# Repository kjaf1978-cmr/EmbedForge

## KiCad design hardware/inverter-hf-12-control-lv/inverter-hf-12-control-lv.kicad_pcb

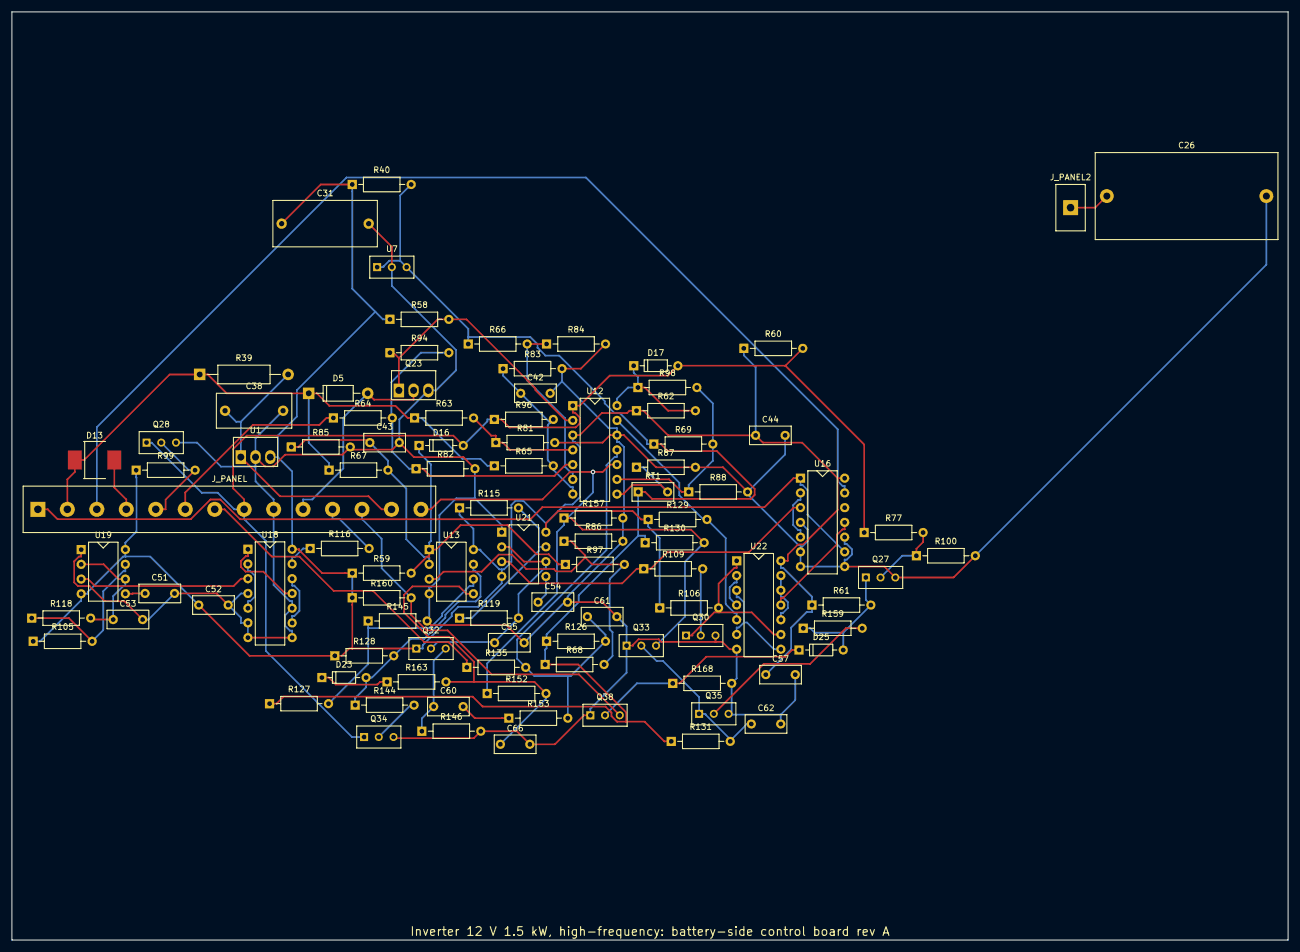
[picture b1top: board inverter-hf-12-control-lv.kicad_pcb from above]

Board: 2 copper layers, 220.0 x 160.0 mm, 96 parts (0 on the bottom side), 61 nets.

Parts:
C26: 33u; C_Film_P27.5
C31: 22u; C_Film_P15
C38: 10u; C_Film_P10
C42, C43: 470n; C_Disc_5.08
C44, C52, C53, C57, C60: 100n; C_Disc_5.08
C51, C54: 10n; C_Disc_5.08
C55: 1n; C_Disc_5.08
C61: 470p; C_Disc_5.08
C62, C66: 220n; C_Disc_5.08
D5: 1N4007; D_DO-41
D13: SS34; D_SMC
D16, D17, D23, D25: 1N4148; D_DO-35
J_PANEL: to the panel; TerminalBlock_1x14
J_PANEL2: to the panel; TerminalBlock_1x1
Q23: IRF540N; TO-220_Vertical
Q27, Q28, Q30, Q32, Q34, Q35: BC547B; TO-92_Wide
Q33: BC557B; TO-92_Wide
Q38: 2N7000; TO-92_Wide
R39: 1; R_Axial_0309
R40, R116: 2.2k; R_Axial_0207
R58, R59, R60, R61, R62, R81, R82, R83, R84, R85, R86, R87, R105, R109, R127, R128, R130, R160, R163: 10k; R_Axial_0207
R63: 49.9k; R_Axial_0207
R64: 45.3k; R_Axial_0207
R65: 39.2k; R_Axial_0207
R66: 1.54k; R_Axial_0207
R67: 51.1k; R_Axial_0207
R68: 715; R_Axial_0207
R69: 3.92k; R_Axial_0207
R77, R100, R144: 47k; R_Axial_0207
R88: 40.2k; R_Axial_0207
R94, R152: 1M; R_Axial_0207
R96: 332k; R_Axial_0207
R97, R131, R159, R168: 100k; R_Axial_0207
R98: 2.2M; R_Axial_0207
R99: 22k; R_Axial_0207
R106, R129, R146: 4.7k; R_Axial_0207
R115: 24.3k; R_Axial_0207
R118: 30.9k; R_Axial_0207
R119: 5.76k; R_Axial_0207
R126: 5.23k; R_Axial_0207
R135: 1k; R_Axial_0207
R145: 30.1k; R_Axial_0207
R153: 3.74k; R_Axial_0207
R157: 33k; R_Axial_0207
RT1: 10k; RT_Disc_5.08
U1: LM2940-9.0; TO-220_Vertical
U7: TL431B; TO-92_Wide
U12: LM339; DIP-14
U13: LM393; DIP-8
U16, U18, U22: V9; DIP-14
U19, U21: NE555; DIP-8

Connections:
A: J_PANEL.1, U16.1, U16.9
AN: U16.2, U16.5
AXA: D5.1, D13.1, J_PANEL.2, R39.1, R63.1, R65.1, R67.1
B: J_PANEL.3, U16.13
BBK: Q30.2, R109.2
BF: D13.2, J_PANEL.4
BKA: J_PANEL.5, Q28.2, R99.2
BLK: Q30.1, R106.2, U22.1, U22.9
BOL: Q34.2, R144.2
BQE: Q27.2, R77.2, R100.1
BSSL: Q35.2, R159.2
BUS: J_PANEL.6, R64.1
C200: U18.3, U19.3
CKB: U16.11, U22.11
CKN: U22.10, U22.12, U22.13
CSF: C61.1, R126.2, R135.2, R153.2, U12.11
CSR: J_PANEL.7, R135.1
D40: R115.2, R119.1, U21.7
D50: R105.2, R118.1, U19.7
ENL: D16.2, D17.2, J_PANEL.8, Q28.1, Q34.1, R60.2, R77.1, R96.1, U12.1
ENNL: D25.2, Q27.1, R61.2, R159.1
GND: C26.2, C31.2, C38.2, C42.2, C43.2, C44.2, C51.2, C52.2, C53.2, C54.2, C55.2, C57.2, C61.2, C62.2, C66.2, J_PANEL.9, Q23.3, Q27.3, Q28.3, Q30.3, Q33.1, Q34.3, Q35.3, Q38.1, R81.2, R82.2, R83.2, R84.2, R85.2, R86.2, R87.2, R88.2, R100.2, R145.2, R146.2, R157.2, R168.2, U1.2, U7.2, U12.12, U13.4, U16.4, U16.6, U16.7, U16.8, U16.10, U18.4, U18.6, U18.7, U18.8, U18.10, U19.1, U21.1, U22.7
HVN: D16.1, R59.2, R97.1, U13.1
K40: C54.1, U21.5
K50: C51.1, U19.5
KC: D5.2, J_PANEL.10, Q23.2
KEN: Q23.1, R58.2, R94.1, U12.2
L50A: J_PANEL.11, R116.2
NHS: R87.1, RT1.2, U12.8
O40: R109.1, U16.3, U21.3
OC: R129.2, U12.13, U22.5
OLF: D23.1, R163.1
OLL: D23.2, R128.2, R144.1, U13.7
Q50: R116.1, U18.13
Q50N: U18.9, U18.12
Q100: U18.1, U18.11
Q100N: U18.2, U18.5
QC: U22.3, U22.6, U22.8
QCN: U22.2, U22.4
SDL: J_PANEL.12, Q38.3, R160.2
SLP: C60.2, R153.1
STOPL: D25.1, Q38.2, R168.1
T40: C55.1, Q32.2, R119.2, U21.2, U21.6
T40E: C60.1, Q32.3, R146.1
T50: C53.1, R118.2, U19.2, U19.6
T90: R69.2, R88.1, R98.2, U12.9
THN: D17.1, R62.2, R98.1, U12.14
V9: C31.1, C44.1, C52.1, C57.1, Q32.1, R40.1, R58.1, R59.1, R60.1, R61.1, R62.1, R99.1, R105.1, R106.1, R115.1, R128.1, R129.1, R160.1, U1.3, U12.3, U13.8, U16.14, U18.14, U19.4, U19.8, U21.4, U21.8, U22.14
V12: C38.1, J_PANEL.13, R39.2, U1.1
VBF: R63.2, R81.1, U12.4
VBH: C43.1, R67.2, R85.1, U13.2
VBS: C42.1, R65.2, R83.1, R96.2, U12.7
VBU: R64.2, R82.1, R94.2, U12.5
VC: J_PANEL.14, Q33.3, R130.2, R152.1, R157.1, U12.10
VCF: C66.1, R152.2, R163.2, U13.5
VHI: R68.2, R86.1, R97.2, U13.3
VLO: R66.2, R84.1, U12.6
VOT: R127.2, R145.1, U13.6
VREFL: R40.2, R66.1, R68.1, R69.1, R126.1, R127.1, R130.1, R131.1, RT1.1, U7.1, U7.3
VSSL: C62.1, Q33.2, Q35.1, R131.2
XB: C26.1, J_PANEL2.1

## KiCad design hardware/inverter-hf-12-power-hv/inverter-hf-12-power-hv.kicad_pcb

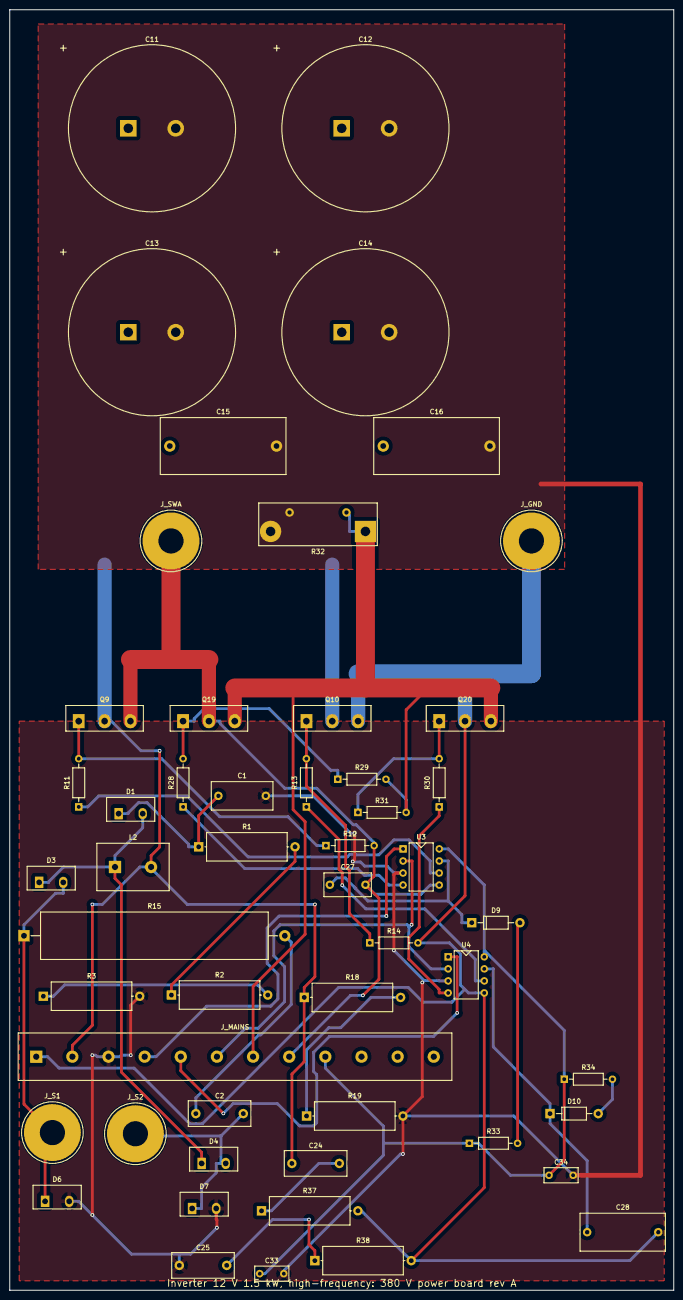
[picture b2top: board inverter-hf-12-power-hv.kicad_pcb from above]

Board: 2 copper layers, 140.0 x 270.0 mm, 52 parts (0 on the bottom side), 31 nets.

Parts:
C1: 100n; C_Film_P10
C2: 220p; C_Disc_P10
C11, C12, C13, C14: 470u; CP_SnapIn_D35
C15, C16: 2.2u; C_Film_P22.5
C24, C25: 2.2n; C_Disc_P10
C27: 2.2u; C_Film_P7.5
C28: 22u; C_Film_P15
C33, C34: 1u; C_Disc_5.08
D1: C4D02120A; TO-220-2_Vertical
D3, D4, D6, D7: C4D20120A; TO-220-2_Vertical
D9, D10: UF4007; D_DO-41
J_GND: GND; Lug_M5
J_MAINS: mains to the panel; TerminalBlock_1x12_P7.62
J_S1: S1; Lug_M5
J_S2: S2; Lug_M5
J_SWA: SWA; Lug_M5
L2: 470u; TerminalBlock_1x2_P7.62
Q9, Q10, Q19, Q20: IKW50N60T; TO-247_Vertical
R1, R2, R3: 150k; R_Axial_P20
R11, R13, R28, R30, R34: 10; R_Axial_0207
R12, R14, R29, R31: 10k; R_Axial_0207
R15: 470; R_Cement_10W
R18, R19: 47k; R_Axial_P20
R32: 4.99m; R_Shunt_4T
R33: 2.2; R_Axial_0207
R37, R38: 220; R_Axial_P20
U3, U4: IR2184-type 600 V; DIP-8

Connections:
BLM: R18.2, R19.1
CL: C1.1, D1.1, R1.1
CL1: R1.2, R2.1
CL2: R2.2, R3.1
GIHA: Q9.1, R11.2, R12.1
GIHB: Q10.1, R13.2, R14.1
GILA: Q19.1, R28.2, R29.1
GILB: Q20.1, R30.2, R31.1
GND: C28.2, J_GND.1, J_MAINS.1, Q10.3, Q20.2, R14.2, R37.2, R38.2, U4.5
HBUS: C11.1, C12.1, C13.1, C14.1, C15.1, C16.1, C24.1, J_MAINS.2, L2.2, Q9.2, Q10.2, R18.1
HOIA: R11.1, U3.6
HOIB: R13.1, U4.6
HVG: C1.2, C11.2, C12.2, C13.2, C14.2, C15.2, C16.2, C25.1, C33.2, C34.2, D6.2, D7.2, J_MAINS.3, R3.2, R19.2, R32.2, R32.4, U3.3, U4.3
INA: J_MAINS.4, U3.1
INB: J_MAINS.5, U4.1
LOIA: R28.1, U3.4
LOIB: R30.1, U4.4
RP: D1.2, D3.1, D4.1, L2.1
S1: D3.2, D6.1, J_S1.1, R15.1
S2: C2.2, D4.2, D7.1, J_S2.1
SD: J_MAINS.6, U3.2, U4.2
SNB: C2.1, R15.2
SRC: J_MAINS.7, Q19.3, Q20.3, R29.2, R31.2, R32.1, R32.3
SWA: C27.2, J_MAINS.8, J_SWA.1, Q9.3, Q19.2, R12.2, U3.5
V15H: C33.1, C34.1, J_MAINS.9, R33.1, R34.1, U3.8, U4.8
VBIA: C27.1, D9.1, U3.7
VBIB: C28.1, D10.1, U4.7
VBRA: D9.2, R33.2
VBRB: D10.2, R34.2
YD1: C24.2, R37.1
YD2: C25.2, R38.1

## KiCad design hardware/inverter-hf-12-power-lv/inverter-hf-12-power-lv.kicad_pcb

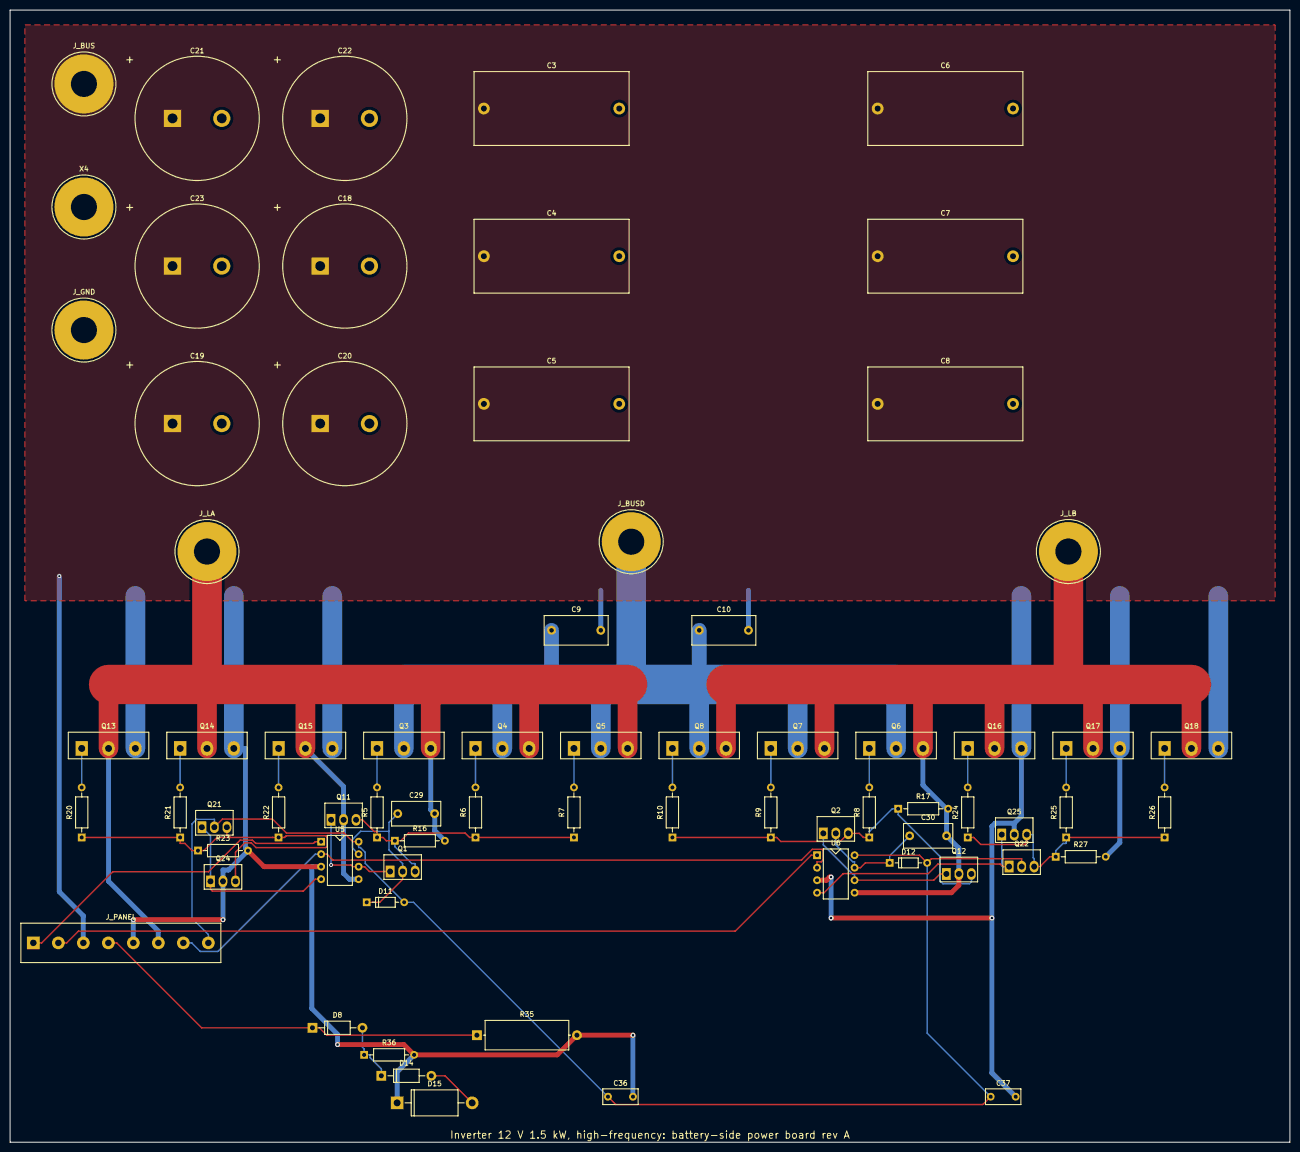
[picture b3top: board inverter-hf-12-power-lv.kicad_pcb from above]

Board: 2 copper layers, 260.0 x 230.0 mm, 70 parts (0 on the bottom side), 34 nets.

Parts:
C3, C4, C5, C6, C7, C8: 47u; C_Film_P27.5
C9, C10: 2.2u; C_Film_P10
C18, C19, C20, C21, C22, C23: 4700u; CP_SnapIn_D25
C29, C30: 2.2u; C_Film_P7.5
C36, C37: 1u; C_Disc_5.08
D8, D14: UF4007; D_DO-41
D11, D12: 1N4148; D_DO-35
D15: 1N5359B; D_DO-201AD
J_BUS: BUS; Lug_M5
J_BUSD: BUSD; Lug_M5
J_GND: GND; Lug_M5
J_LA: LA; Lug_M5
J_LB: LB; Lug_M5
J_PANEL: to the panel; TerminalBlock_1x8
Q1, Q2, Q21, Q22: D44H11; TO-220_Vertical
Q3, Q4, Q5, Q6, Q7, Q8, Q13, Q14, Q15, Q16, Q17, Q18: IRFP4468; TO-247_Vertical
Q11, Q12, Q24, Q25: D45H11; TO-220_Vertical
R5, R6, R7, R8, R9, R10, R20, R21, R22, R24, R25, R26: 4.7; R_Axial_0207
R16, R17, R23, R27: 10k; R_Axial_0207
R35: 0.68; R_Axial_P20
R36: 1k; R_Axial_0207
U5, U6: IR2184-type 600 V; DIP-8
X4: BAT-; Lug_M5

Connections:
A: J_PANEL.1, U5.1
B: J_PANEL.2, U6.1
BUS: C3.1, C4.1, C5.1, C6.1, C7.1, C8.1, C18.1, C19.1, C20.1, C21.1, C22.1, C23.1, J_BUS.1, J_PANEL.3
BUSD: C9.1, C10.1, J_BUSD.1, Q3.2, Q4.2, Q5.2, Q6.2, Q7.2, Q8.2
CSR: D8.1, J_PANEL.4, R35.1
CTA: D8.2, D14.1, R36.1
CZC: D14.2, D15.2
EHA: Q1.3, Q11.3, R5.1, R6.1, R7.1, R16.1
EHB: Q2.3, Q12.3, R8.1, R9.1, R10.1, R17.1
ELA: Q21.3, Q24.3, R20.1, R21.1, R22.1, R23.1
ELB: Q22.3, Q25.3, R24.1, R25.1, R26.1, R27.1
GHA1: Q3.1, R5.2
GHA2: Q4.1, R6.2
GHA3: Q5.1, R7.2
GHB1: Q6.1, R8.2
GHB2: Q7.1, R9.2
GHB3: Q8.1, R10.2
GLA1: Q13.1, R20.2
GLA2: Q14.1, R21.2
GLA3: Q15.1, R22.2
GLB1: Q16.1, R24.2
GLB2: Q17.1, R25.2
GLB3: Q18.1, R26.2
GND: C3.2, C4.2, C5.2, C6.2, C7.2, C8.2, C9.2, C10.2, C18.2, C19.2, C20.2, C21.2, C22.2, C23.2, C36.2, C37.2, D15.1, J_GND.1, J_PANEL.5, Q13.3, Q14.3, Q15.3, Q16.3, Q17.3, Q18.3, Q24.2, Q25.2, R23.2, R27.2, R35.2, R36.2, U5.3, U6.3, X4.1
HOA: Q1.1, Q11.1, U5.6
HOB: Q2.1, Q12.1, U6.6
LA: C29.2, J_LA.1, J_PANEL.6, Q3.3, Q4.3, Q5.3, Q11.2, Q13.2, Q14.2, Q15.2, R16.2, U5.5
LB: C30.2, J_LB.1, Q6.3, Q7.3, Q8.3, Q12.2, Q16.2, Q17.2, Q18.2, R17.2, U6.5
LOA: Q21.1, Q24.1, U5.4
LOB: Q22.1, Q25.1, U6.4
SDL: J_PANEL.7, U5.2, U6.2
V12: C36.1, C37.1, D11.2, D12.2, J_PANEL.8, Q21.2, Q22.2, U5.8, U6.8
VBA: C29.1, D11.1, Q1.2, U5.7
VBB: C30.1, D12.1, Q2.2, U6.7

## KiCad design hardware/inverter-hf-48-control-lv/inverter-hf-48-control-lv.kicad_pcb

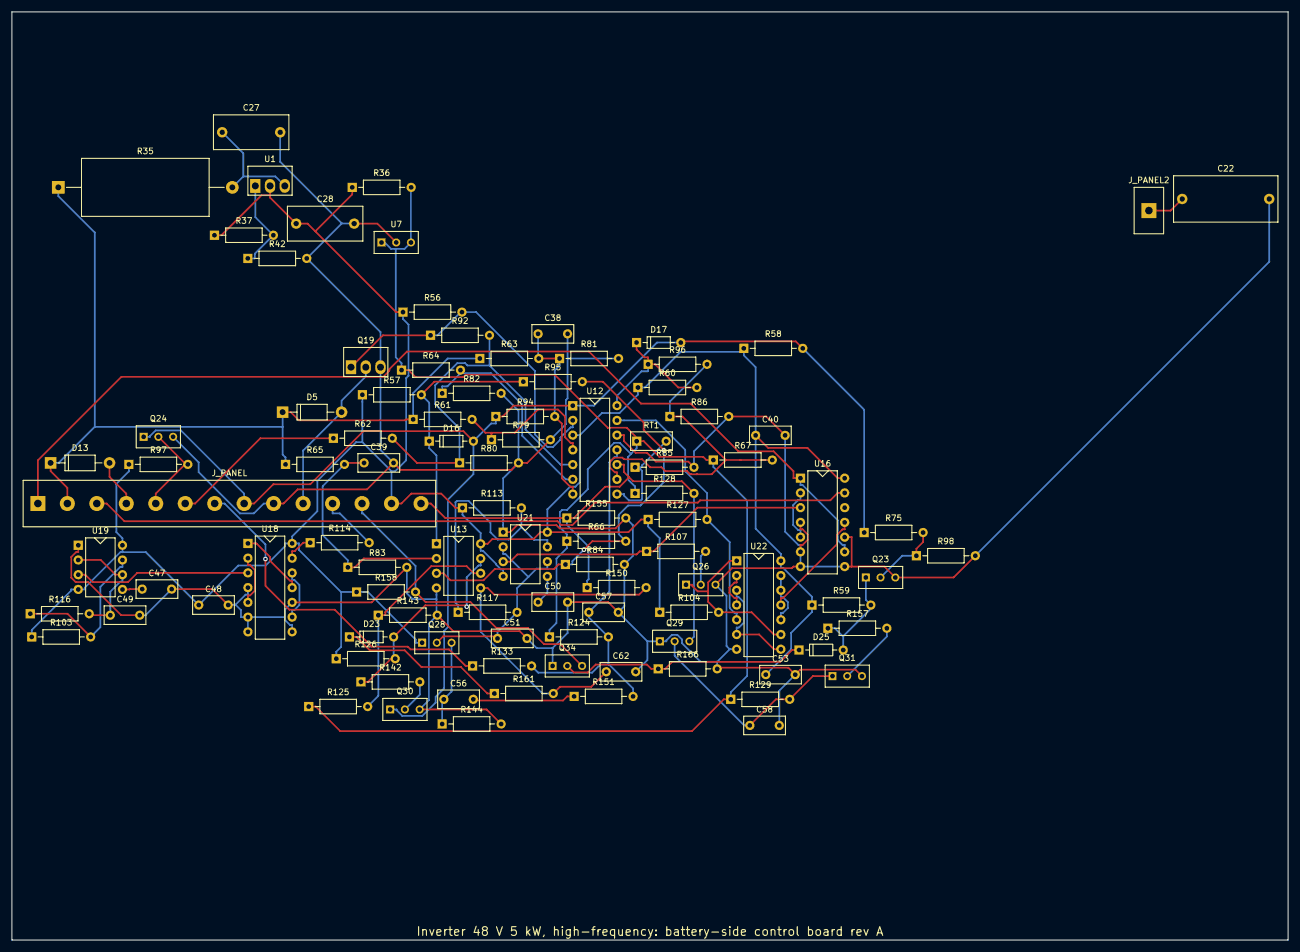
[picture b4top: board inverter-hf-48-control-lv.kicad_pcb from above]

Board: 2 copper layers, 220.0 x 160.0 mm, 98 parts (0 on the bottom side), 62 nets.

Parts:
C22: 2.2u; C_Film_P15
C27: 2.2u; C_Film_P10
C28: 10u; C_Film_P10
C38, C39: 470n; C_Disc_5.08
C40, C48, C49, C53, C56: 100n; C_Disc_5.08
C47, C50: 10n; C_Disc_5.08
C51: 1n; C_Disc_5.08
C57: 470p; C_Disc_5.08
C58, C62: 220n; C_Disc_5.08
D5, D13: 1N4007; D_DO-41
D16, D17, D23, D25: 1N4148; D_DO-35
J_PANEL: to the panel; TerminalBlock_1x14
J_PANEL2: to the panel; TerminalBlock_1x1
Q19: IRF540N; TO-220_Vertical
Q23, Q24, Q26, Q28, Q30, Q31: BC547B; TO-92_Wide
Q29: BC557B; TO-92_Wide
Q34: 2N7000; TO-92_Wide
R35: 220; R_Cement_5W
R36, R114: 2.2k; R_Axial_0207
R37: 240; R_Axial_0207
R42: 2.05k; R_Axial_0207
R56, R57, R58, R59, R60, R79, R80, R81, R82, R83, R84, R85, R103, R107, R125, R126, R128, R158, R161: 10k; R_Axial_0207
R61, R63: 200k; R_Axial_0207
R62: 182k; R_Axial_0207
R64: 1.54k; R_Axial_0207
R65: 243k; R_Axial_0207
R66: 715; R_Axial_0207
R67: 3.92k; R_Axial_0207
R75, R98, R142: 47k; R_Axial_0207
R86: 40.2k; R_Axial_0207
R92, R150: 1M; R_Axial_0207
R94: 475k; R_Axial_0207
R95, R129, R157, R166: 100k; R_Axial_0207
R96: 2.2M; R_Axial_0207
R97: 22k; R_Axial_0207
R104, R127, R144: 4.7k; R_Axial_0207
R113: 24.3k; R_Axial_0207
R116: 30.9k; R_Axial_0207
R117: 5.76k; R_Axial_0207
R124: 5.23k; R_Axial_0207
R133: 1k; R_Axial_0207
R143: 30.1k; R_Axial_0207
R151: 4.99k; R_Axial_0207
R155: 33k; R_Axial_0207
RT1: 10k; RT_Disc_5.08
U1: LM317HV; TO-220_Vertical
U7: TL431B; TO-92_Wide
U12: LM339; DIP-14
U13: LM393; DIP-8
U16, U18, U22: V12; DIP-14
U19, U21: NE555; DIP-8

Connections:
A: J_PANEL.1, U16.1, U16.9
ADJ: R37.2, R42.1, U1.1
AN: U16.2, U16.5
AXA: D5.1, D13.1, J_PANEL.2, R35.1, R61.1, R63.1, R65.1
B: J_PANEL.3, U16.13
BBK: Q26.2, R107.2
BF: D13.2, J_PANEL.4
BKA: J_PANEL.5, Q24.2, R97.2
BLK: Q26.1, R104.2, U22.1, U22.9
BOL: Q30.2, R142.2
BQE: Q23.2, R75.2, R98.1
BSSL: Q31.2, R157.2
BUS: J_PANEL.6, R62.1
C200: U18.3, U19.3
CKB: U16.11, U22.11
CKN: U22.10, U22.12, U22.13
CSF: C57.1, R124.2, R133.2, R151.2, U12.11
CSR: J_PANEL.7, R133.1
D40: R113.2, R117.1, U21.7
D50: R103.2, R116.1, U19.7
ENL: D16.2, D17.2, J_PANEL.8, Q24.1, Q30.1, R58.2, R75.1, R94.1, U12.1
ENNL: D25.2, Q23.1, R59.2, R157.1
GND: C22.2, C27.2, C28.2, C38.2, C39.2, C40.2, C47.2, C48.2, C49.2, C50.2, C51.2, C53.2, C57.2, C58.2, C62.2, J_PANEL.9, Q19.3, Q23.3, Q24.3, Q26.3, Q29.1, Q30.3, Q31.3, Q34.1, R42.2, R79.2, R80.2, R81.2, R82.2, R83.2, R84.2, R85.2, R86.2, R98.2, R143.2, R144.2, R155.2, R166.2, U7.2, U12.12, U13.4, U16.4, U16.6, U16.7, U16.8, U16.10, U18.4, U18.6, U18.7, U18.8, U18.10, U19.1, U21.1, U22.7
HVN: D16.1, R57.2, R95.1, U13.1
K40: C50.1, U21.5
K50: C47.1, U19.5
KC: D5.2, J_PANEL.10, Q19.2
KEN: Q19.1, R56.2, R92.1, U12.2
L50A: J_PANEL.11, R114.2
NHS: R85.1, RT1.2, U12.8
O40: R107.1, U16.3, U21.3
OC: R127.2, U12.13, U22.5
OLF: D23.1, R161.1
OLL: D23.2, R126.2, R142.1, U13.7
Q50: R114.1, U18.13
Q50N: U18.9, U18.12
Q100: U18.1, U18.11
Q100N: U18.2, U18.5
QC: U22.3, U22.6, U22.8
QCN: U22.2, U22.4
SDL: J_PANEL.12, Q34.3, R158.2
SLP: C56.2, R151.1
STOPL: D25.1, Q34.2, R166.1
T40: C51.1, Q28.2, R117.2, U21.2, U21.6
T40E: C56.1, Q28.3, R144.1
T50: C49.1, R116.2, U19.2, U19.6
T90: R67.2, R86.1, R96.2, U12.9
THN: D17.1, R60.2, R96.1, U12.14
V12: C28.1, C40.1, C48.1, C53.1, J_PANEL.13, Q28.1, R36.1, R37.1, R56.1, R57.1, R58.1, R59.1, R60.1, R97.1, R103.1, R104.1, R113.1, R126.1, R127.1, R158.1, U1.2, U12.3, U13.8, U16.14, U18.14, U19.4, U19.8, U21.4, U21.8, U22.14
VBF: R61.2, R79.1, U12.4
VBH: C39.1, R65.2, R83.1, U13.2
VBS: C38.1, R63.2, R81.1, R94.2, U12.7
VBU: R62.2, R80.1, R92.2, U12.5
VC: J_PANEL.14, Q29.3, R128.2, R150.1, R155.1, U12.10
VCF: C62.1, R150.2, R161.2, U13.5
VHI: R66.2, R84.1, R95.2, U13.3
VLO: R64.2, R82.1, U12.6
VOT: R125.2, R143.1, U13.6
VRAW: C27.1, R35.2, U1.3
VREFL: R36.2, R64.1, R66.1, R67.1, R124.1, R125.1, R128.1, R129.1, RT1.1, U7.1, U7.3
VSSL: C58.1, Q29.2, Q31.1, R129.2
XB: C22.1, J_PANEL2.1

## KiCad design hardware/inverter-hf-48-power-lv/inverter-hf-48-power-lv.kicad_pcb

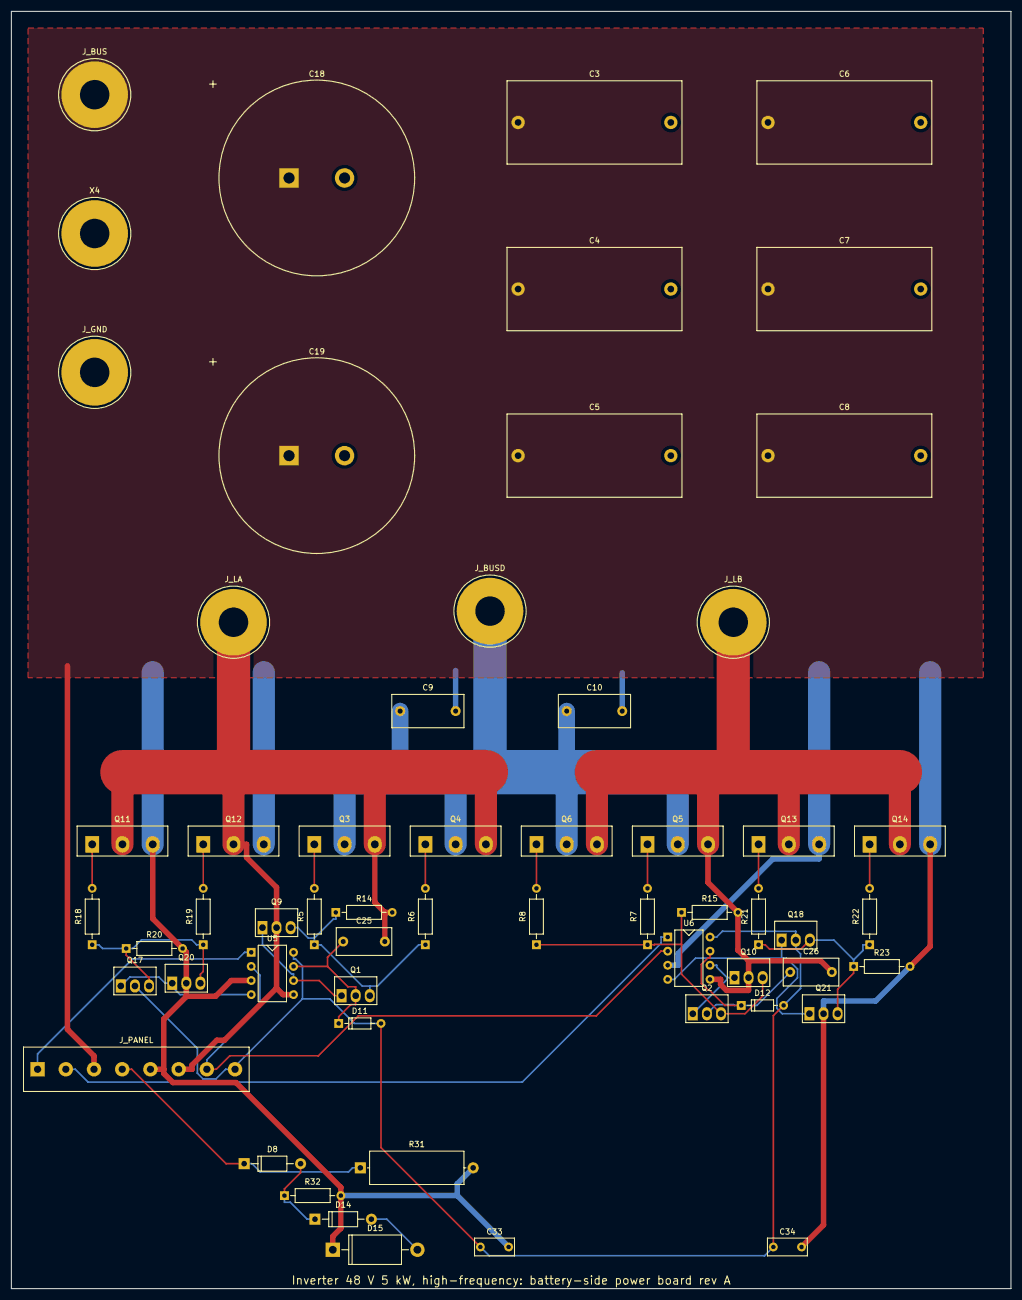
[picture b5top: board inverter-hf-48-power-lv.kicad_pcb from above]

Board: 2 copper layers, 180.0 x 230.0 mm, 58 parts (0 on the bottom side), 30 nets.

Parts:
C3, C4, C5, C6, C7, C8: 47u; C_Film_P27.5
C9, C10: 2.2u; C_Film_P10
C18, C19: 2200u; CP_SnapIn_D35
C25, C26: 2.2u; C_Film_P7.5
C33, C34: 1u; C_Disc_5.08
D8, D14: UF4007; D_DO-41
D11, D12: 1N4148; D_DO-35
D15: 1N5359B; D_DO-201AD
J_BUS: BUS; Lug_M5
J_BUSD: BUSD; Lug_M5
J_GND: GND; Lug_M5
J_LA: LA; Lug_M5
J_LB: LB; Lug_M5
J_PANEL: to the panel; TerminalBlock_1x8
Q1, Q2, Q17, Q18: D44H11; TO-220_Vertical
Q3, Q4, Q5, Q6, Q11, Q12, Q13, Q14: IRFP4468; TO-247_Vertical
Q9, Q10, Q20, Q21: D45H11; TO-220_Vertical
R5, R6, R7, R8, R18, R19, R21, R22: 4.7; R_Axial_0207
R14, R15, R20, R23: 10k; R_Axial_0207
R31: 1.2; R_Axial_P20
R32: 1k; R_Axial_0207
U5, U6: IR2184-type 600 V; DIP-8
X4: BAT-; Lug_M5

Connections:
A: J_PANEL.1, U5.1
B: J_PANEL.2, U6.1
BUS: C3.1, C4.1, C5.1, C6.1, C7.1, C8.1, C18.1, C19.1, J_BUS.1, J_PANEL.3
BUSD: C9.1, C10.1, J_BUSD.1, Q3.2, Q4.2, Q5.2, Q6.2
CSR: D8.1, J_PANEL.4, R31.1
CTA: D8.2, D14.1, R32.1
CZC: D14.2, D15.2
EHA: Q1.3, Q9.3, R5.1, R6.1, R14.1
EHB: Q2.3, Q10.3, R7.1, R8.1, R15.1
ELA: Q17.3, Q20.3, R18.1, R19.1, R20.1
ELB: Q18.3, Q21.3, R21.1, R22.1, R23.1
GHA1: Q3.1, R5.2
GHA2: Q4.1, R6.2
GHB1: Q5.1, R7.2
GHB2: Q6.1, R8.2
GLA1: Q11.1, R18.2
GLA2: Q12.1, R19.2
GLB1: Q13.1, R21.2
GLB2: Q14.1, R22.2
GND: C3.2, C4.2, C5.2, C6.2, C7.2, C8.2, C9.2, C10.2, C18.2, C19.2, C33.2, C34.2, D15.1, J_GND.1, J_PANEL.5, Q11.3, Q12.3, Q13.3, Q14.3, Q20.2, Q21.2, R20.2, R23.2, R31.2, R32.2, U5.3, U6.3, X4.1
HOA: Q1.1, Q9.1, U5.6
HOB: Q2.1, Q10.1, U6.6
LA: C25.2, J_LA.1, J_PANEL.6, Q3.3, Q4.3, Q9.2, Q11.2, Q12.2, R14.2, U5.5
LB: C26.2, J_LB.1, Q5.3, Q6.3, Q10.2, Q13.2, Q14.2, R15.2, U6.5
LOA: Q17.1, Q20.1, U5.4
LOB: Q18.1, Q21.1, U6.4
SDL: J_PANEL.7, U5.2, U6.2
V12: C33.1, C34.1, D11.2, D12.2, J_PANEL.8, Q17.2, Q18.2, U5.8, U6.8
VBA: C25.1, D11.1, Q1.2, U5.7
VBB: C26.1, D12.1, Q2.2, U6.7

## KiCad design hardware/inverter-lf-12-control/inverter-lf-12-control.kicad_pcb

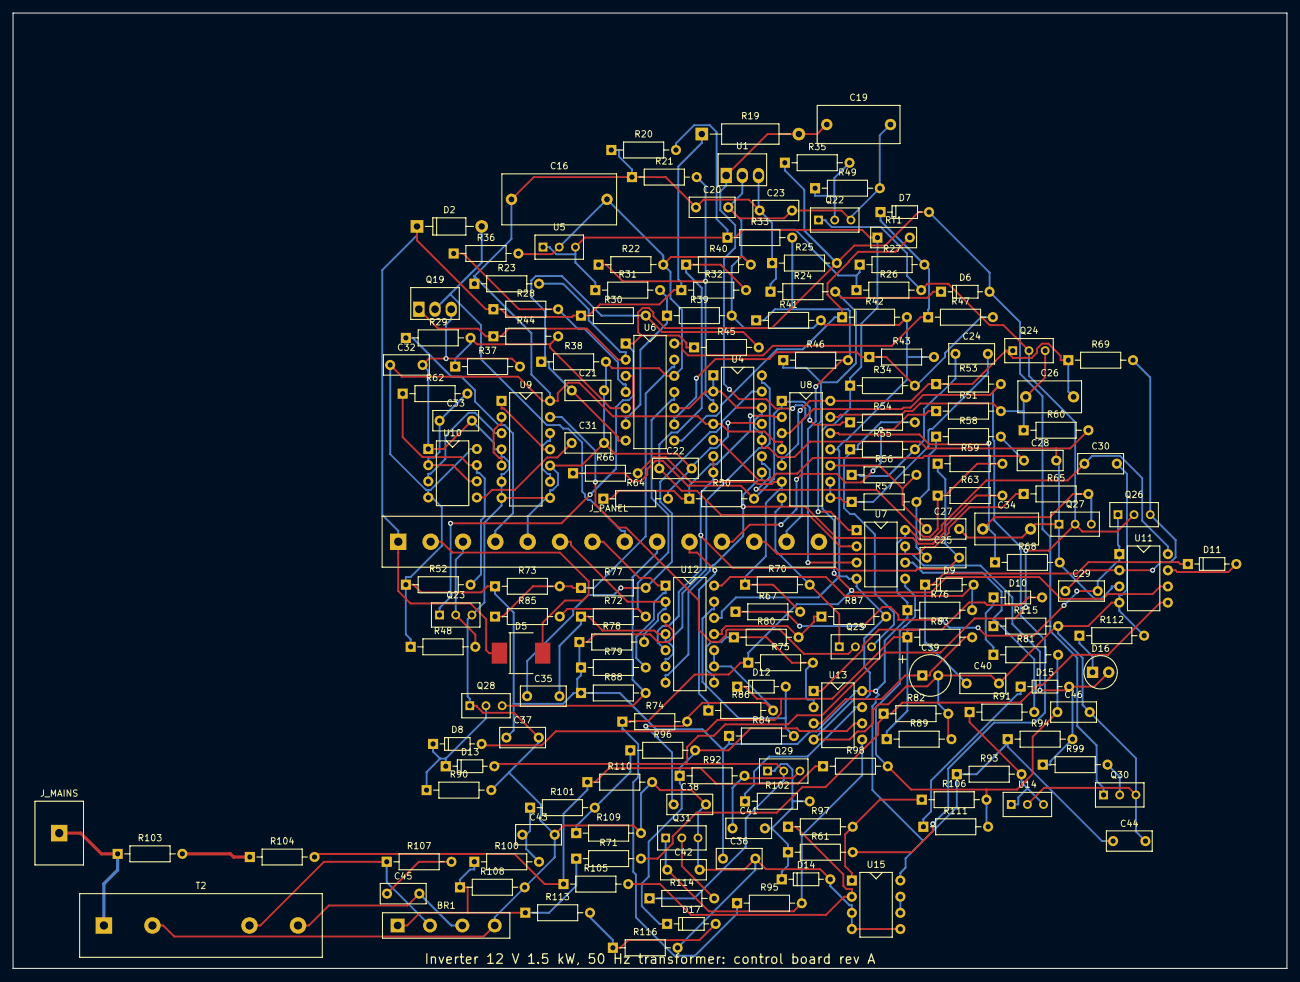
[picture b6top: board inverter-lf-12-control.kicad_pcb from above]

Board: 2 copper layers, 200.0 x 150.0 mm, 170 parts (0 on the bottom side), 100 nets.

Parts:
BR1: DB107; Bridge_Inline_4
C16: 22u; C_Film_P15
C19: 10u; C_Film_P10
C20, C23, C27, C30, C32, C33, C36, C37, C44, C45: 100n; C_Disc_5.08
C21, C22, C42: 470n; C_Disc_5.08
C24: 110n; C_Disc_5.08
C25: 270n; C_Disc_5.08
C26, C34: 3.3u; C_Film_P7.5
C28: 39n; C_Disc_5.08
C29, C43, C46: 1u; C_Disc_5.08
C31: 10n; C_Disc_5.08
C35: 3.3n; C_Disc_5.08
C38: 47p; C_Disc_5.08
C39: 22u; CP_Radial_D6.3
C40: 150p; C_Disc_5.08
C41: 220n; C_Disc_5.08
D2: 1N4007; D_DO-41
D5: SS34; D_SMC
D6, D7, D8, D9, D10, D11, D12, D13, D15, D17: 1N4148; D_DO-35
D14: BZX55C3V3; D_DO-35
D16: red; LED_D5.0
J_MAINS: mains to the panel; TerminalBlock_1x1_P7.62
J_PANEL: to the panel; TerminalBlock_1x14
Q19: IRF540N; TO-220_Vertical
Q22, Q23, Q30, Q31: BC547B; TO-92_Wide
Q24, Q25, Q26, Q27, Q28, Q29: 2N7000; TO-92_Wide
R19: 1; R_Axial_0309
R20, R76, R84, R93, R94: 2.2k; R_Axial_0207
R21, R22, R23, R24, R25, R26, R27, R36, R37, R38, R39, R40, R41, R42, R52, R59, R63, R64, R66, R67, R70, R72, R77, R82, R86, R88, R99, R100, R110, R111, R115, R116: 10k; R_Axial_0207
R28: 49.9k; R_Axial_0207
R29: 45.3k; R_Axial_0207
R30: 39.2k; R_Axial_0207
R31: 1.54k; R_Axial_0207
R32: 51.1k; R_Axial_0207
R33: 715; R_Axial_0207
R34: 3.92k; R_Axial_0207
R35, R49, R60, R68, R92: 47k; R_Axial_0207
R43: 40.2k; R_Axial_0207
R44: 1M; R_Axial_0207
R45: 332k; R_Axial_0207
R46, R53, R89, R90, R95, R96, R97, R105, R106, R114: 100k; R_Axial_0207
R47: 2.2M; R_Axial_0207
R48: 22k; R_Axial_0207
R50: 4.99k; R_Axial_0207
R51, R65: 118k; R_Axial_0207
R54, R107: 220; R_Axial_0207
R55, R56, R57, R58: 22.1k; R_Axial_0207
R61, R98: 200k; R_Axial_0207
R62: 30.9k; R_Axial_0207
R69: 33k; R_Axial_0207
R71: 54.9k; R_Axial_0207
R73, R102, R108: 1k; R_Axial_0207
R74: 90.9k; R_Axial_0207
R75: 86.6k; R_Axial_0207
R78, R79, R81, R112: 4.7k; R_Axial_0207
R80: 8.87k; R_Axial_0207
R83: 220k; R_Axial_0207
R85: 28.7k; R_Axial_0207
R87: 5.62k; R_Axial_0207
R91: 21.5k; R_Axial_0207
R101: 57.6k; R_Axial_0207
R103, R104: 470k; R_Axial_0207
R109: 25.5k; R_Axial_0207
R113: 47.5k; R_Axial_0207
RT1: 10k; RT_Disc_5.08
T2: 0.052; Transformer_Wires_P7.62
U1: LM2940-9.0; TO-220_Vertical
U4, U8: TL074; DIP-14
U5: TL431B; TO-92_Wide
U6, U12: LM339; DIP-14
U7: LM393; DIP-8
U9: V9; DIP-14
U10: NE555; DIP-8
U11, U13, U15: LM358; DIP-8
U14: TL431; TO-92_Wide

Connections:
AXA: D2.1, D5.1, J_PANEL.1, R19.1, R28.1, R30.1, R32.1
BF: D5.2, J_PANEL.2
BFL: Q30.2, R99.2
BKA: J_PANEL.3, Q23.2, R48.2
BQE: Q22.2, R35.2, R49.1
BSS: Q31.2, R114.2
BUS: J_PANEL.4, R29.1
C200: U9.3, U10.3
D50: R52.2, R62.1, U10.7
DV1: R103.2, R104.1
DVN: R98.1, R104.2, R105.1, R110.1
EN: D6.2, D7.2, Q23.1, Q30.1, R25.2, R35.1, R45.1, U6.1
ENN: D13.2, Q22.1, Q24.2, Q26.2, Q27.2, Q29.2, R26.2, R114.1
F1A: C24.1, R55.2, R56.1
F1B: C27.1, R56.2, U8.10
F1O: C24.2, R57.1, U8.8, U8.9
F2A: C25.1, R57.2, R58.1
F2B: C28.1, R58.2, U4.5
FEA: C41.1, Q29.3, R92.2
FLT: D15.2, D16.2, R94.2, R99.1, U7.7
GND: BR1.4, C16.2, C19.2, C20.2, C21.2, C22.2, C23.2, C30.2, C31.2, C32.2, C33.2, C36.2, C37.2, C38.2, C39.2, C40.2, C42.2, C43.2, C44.2, C46.2, D14.2, J_PANEL.5, Q19.3, Q22.3, Q23.3, Q28.1, Q30.3, Q31.3, R22.2, R36.2, R37.2, R38.2, R39.2, R40.2, R41.2, R42.2, R43.2, R49.2, R64.2, R82.2, R87.2, R89.2, R90.2, R108.2, R109.2, R110.2, R112.2, R115.2, R116.2, T2.2, U1.2, U4.11, U5.2, U6.12, U7.4, U8.11, U9.4, U9.6, U9.7, U9.8, U9.10, U10.1, U11.4, U12.12, U13.4, U14.2, U15.3, U15.4, U15.5
H: R50.2, R54.1, R66.1, U8.1
HN: R50.1, R64.1, U8.2
HP: R53.2, R61.2, U8.3
HVN: D6.1, R24.2, R46.1, U7.1
INA: J_PANEL.6, R78.2, U12.2
INB: J_PANEL.7, R79.2, U12.1
K50: C31.1, U10.5
KC: D2.2, J_PANEL.8, Q19.2
KEN: Q19.1, R23.2, R44.1, U6.2
L: Q25.1, R70.2, U8.7
LAT: D15.1, R111.1
LFA: D16.1, R112.1
LN: R66.2, R67.2, R70.1, U8.6
NDC: C26.1, Q24.3, R51.2, R60.1, U8.13
NEA: D17.1, R92.1, R96.2, U13.6
NFX: C29.1, Q26.3, R69.2, U11.2
NHS: R42.1, RT1.2, U6.8
NSB: R59.2, R63.1, U4.9
NTI: C35.1, R77.2, U4.13
OCH: R75.2, R80.1, U12.8, U13.2
OCL: R80.2, R87.1, U12.11
OCN: D12.2, R84.2, U12.13
OCP: D9.2, R76.2, U12.14
OCS: C40.1, D8.2, D9.1, D11.1, D12.1, R83.1, R89.1
OLC: C39.1, R83.2, U13.3
OLO: D10.2, U13.1
OLS: D10.1, R81.1
OUTL: J_MAINS.1, R103.1, T2.1
OVC: D11.2, U11.7
PDC: C34.1, Q27.3, R65.2, R68.1, U8.12
PLA: D17.2, R113.2, R116.1
PRN: R97.1, R105.2, U15.2
PRO: R97.2, R106.1, U15.1
PST: R72.2, R85.2, U6.11
Q50: Q25.2, U9.13
Q50N: U9.9, U9.12
Q100: U9.1, U9.11
Q100N: U9.2, U9.5
SAO: BR1.2, R107.1, T2.3
SBO: BR1.3, C45.2, T2.4
SD: J_PANEL.9, Q28.3, R88.2
SINE: C25.2, R59.1, U4.6, U4.7, U12.5
SINEB: R63.2, U4.8, U12.7
SNO: C45.1, R107.2
SO: R96.1, R101.2, R109.1
SP: C46.1, R81.2, R98.2, R106.2, R111.2, U7.5
SPRO: U15.6, U15.7
SQ: Q25.3, R54.2, R55.1
SQT: R73.2, R77.1, R85.1, U6.13
SRC: J_PANEL.10, R86.1
SRS: C38.1, R74.2, R86.2, U12.9, U12.10
STOP: D8.1, D13.1, Q28.2, R90.1
SWA: J_PANEL.11, R51.1
SWB: J_PANEL.12, R65.1
T50: C33.1, R62.2, U10.2, U10.6
T90: R34.2, R43.1, R47.2, U6.9
THN: D7.1, R27.2, R47.1, U6.14
TRI: C35.2, R72.1, U4.14, U12.4, U12.6
V9: C16.1, C20.1, C23.1, C30.1, C32.1, C36.1, C37.1, C44.1, R20.1, R21.1, R23.1, R24.1, R25.1, R26.1, R27.1, R48.1, R52.1, R73.1, R76.1, R78.1, R79.1, R84.1, R88.1, R93.1, R94.1, U1.3, U4.4, U6.3, U7.8, U8.4, U9.14, U10.4, U10.8, U11.8, U12.3, U13.8, U15.8
V12: C19.1, J_PANEL.13, R19.2, U1.1
VA: C41.2, D14.1, Q29.1, R61.1, R102.2
VAO: R102.1, U13.7
VBF: R28.2, R36.1, U6.4
VBH: C22.1, R32.2, R40.1, U7.2
VBS: C21.1, R30.2, R38.1, R45.2, U6.7
VBU: R29.2, R37.1, R44.2, U6.5
VFX: C29.2, Q26.1, R67.1, U11.1
VHI: R33.2, R41.1, R46.2, U7.3
VLC: R71.2, R82.1, U11.5
VLO: R31.2, R39.1, U6.6
VME: C26.2, Q24.1, R53.1, R69.1, U8.5, U8.14
VMID: C27.2, C28.2, C34.2, Q27.1, R60.2, R68.2, U4.1, U4.2, U4.10, U4.12, U6.10, U11.3
VMR: R21.2, R22.1, U4.3
VREF: R20.2, R31.1, R33.1, R34.1, R74.1, R75.1, R95.1, RT1.1, U5.1, U5.3, U11.6
VREF2: R91.1, R93.2, U14.1, U14.3
VRO: BR1.1, R71.1, R100.1, R108.1, R113.1
VRP: R91.2, R115.1, U7.6
VSO: C43.1, R100.2, R101.1
VSS: C42.1, Q31.1, R95.2, U13.5

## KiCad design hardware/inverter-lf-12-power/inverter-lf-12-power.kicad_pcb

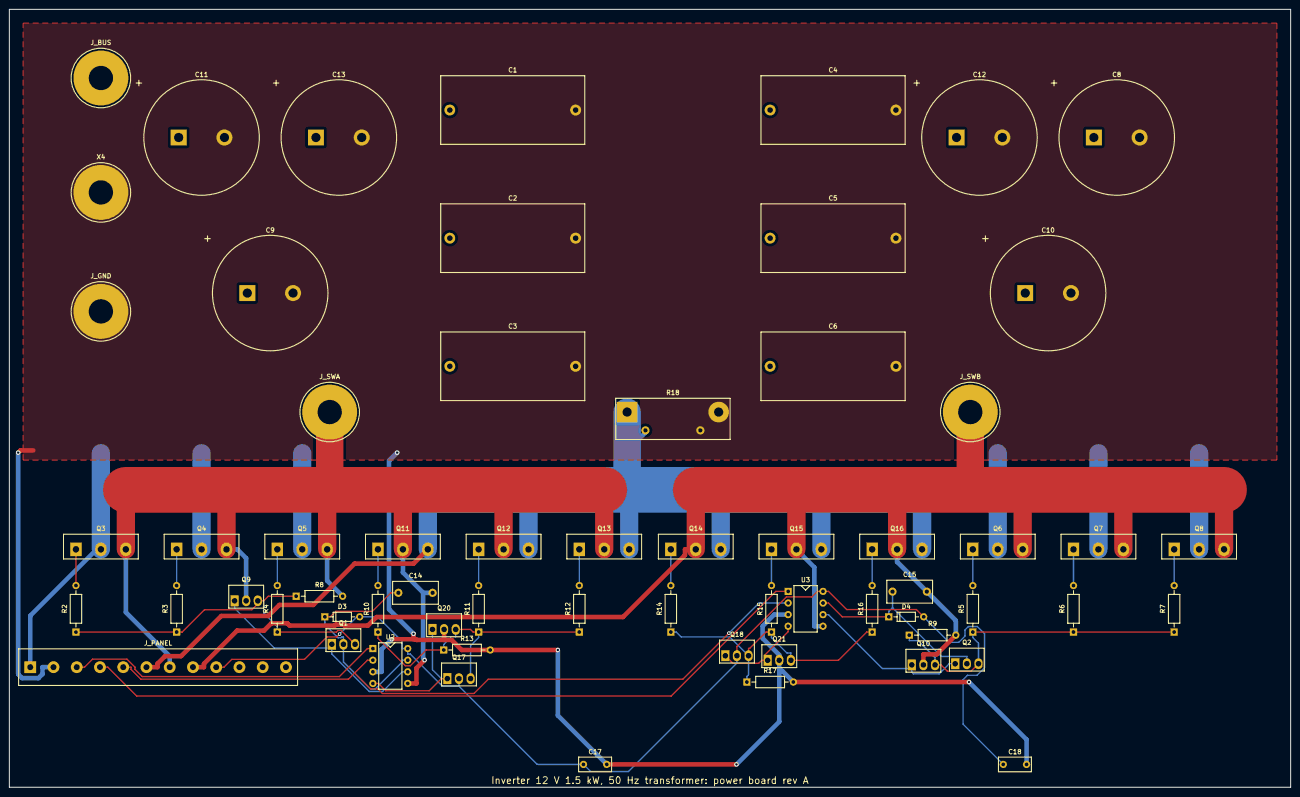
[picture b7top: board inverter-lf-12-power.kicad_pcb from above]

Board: 2 copper layers, 280.0 x 170.0 mm, 63 parts (0 on the bottom side), 31 nets.

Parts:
C1, C2, C3, C4, C5, C6: 47u; C_Film_P27.5
C8, C9, C10, C11, C12, C13: 4700u; CP_SnapIn_D25
C14, C15: 2.2u; C_Film_P7.5
C17, C18: 1u; C_Disc_5.08
D3, D4: 1N4148; D_DO-35
J_BUS: BUS; Lug_M5
J_GND: GND; Lug_M5
J_PANEL: to the panel; TerminalBlock_1x12
J_SWA: SWA; Lug_M5
J_SWB: SWB; Lug_M5
Q1, Q2, Q17, Q18: D44H11; TO-220_Vertical
Q3, Q4, Q5, Q6, Q7, Q8, Q11, Q12, Q13, Q14, Q15, Q16: IRFP4468; TO-247_Vertical
Q9, Q10, Q20, Q21: D45H11; TO-220_Vertical
R2, R3, R4, R5, R6, R7, R10, R11, R12, R14, R15, R16: 4.7; R_Axial_0207
R8, R9, R13, R17: 10k; R_Axial_0207
R18: 0.2m; R_Shunt_4T
U2, U3: IR2184-type 600 V; DIP-8
X4: BAT-; Lug_M5

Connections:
BUS: C1.1, C2.1, C3.1, C4.1, C5.1, C6.1, C8.1, C9.1, C10.1, C11.1, C12.1, C13.1, J_BUS.1, J_PANEL.1, Q3.2, Q4.2, Q5.2, Q6.2, Q7.2, Q8.2
EHA: Q1.3, Q9.3, R2.1, R3.1, R4.1, R8.1
EHB: Q2.3, Q10.3, R5.1, R6.1, R7.1, R9.1
ELA: Q17.3, Q20.3, R10.1, R11.1, R12.1, R13.1
ELB: Q18.3, Q21.3, R14.1, R15.1, R16.1, R17.1
GHA1: Q3.1, R2.2
GHA2: Q4.1, R3.2
GHA3: Q5.1, R4.2
GHB1: Q6.1, R5.2
GHB2: Q7.1, R6.2
GHB3: Q8.1, R7.2
GLA1: Q11.1, R10.2
GLA2: Q12.1, R11.2
GLA3: Q13.1, R12.2
GLB1: Q14.1, R14.2
GLB2: Q15.1, R15.2
GLB3: Q16.1, R16.2
GND: C1.2, C2.2, C3.2, C4.2, C5.2, C6.2, C8.2, C9.2, C10.2, C11.2, C12.2, C13.2, C17.2, C18.2, J_GND.1, J_PANEL.2, Q20.2, Q21.2, R13.2, R17.2, R18.2, R18.4, U2.3, U3.3, X4.1
HOA: Q1.1, Q9.1, U2.6
HOB: Q2.1, Q10.1, U3.6
INA: J_PANEL.3, U2.1
INB: J_PANEL.4, U3.1
LOA: Q17.1, Q20.1, U2.4
LOB: Q18.1, Q21.1, U3.4
SD: J_PANEL.5, U2.2, U3.2
SRC: J_PANEL.6, Q11.3, Q12.3, Q13.3, Q14.3, Q15.3, Q16.3, R18.1, R18.3
SWA: C14.2, J_PANEL.7, J_SWA.1, Q3.3, Q4.3, Q5.3, Q9.2, Q11.2, Q12.2, Q13.2, R8.2, U2.5
SWB: C15.2, J_PANEL.8, J_SWB.1, Q6.3, Q7.3, Q8.3, Q10.2, Q14.2, Q15.2, Q16.2, R9.2, U3.5
V12: C17.1, C18.1, D3.2, D4.2, J_PANEL.9, Q17.2, Q18.2, U2.8, U3.8
VBA: C14.1, D3.1, Q1.2, U2.7
VBB: C15.1, D4.1, Q2.2, U3.7
